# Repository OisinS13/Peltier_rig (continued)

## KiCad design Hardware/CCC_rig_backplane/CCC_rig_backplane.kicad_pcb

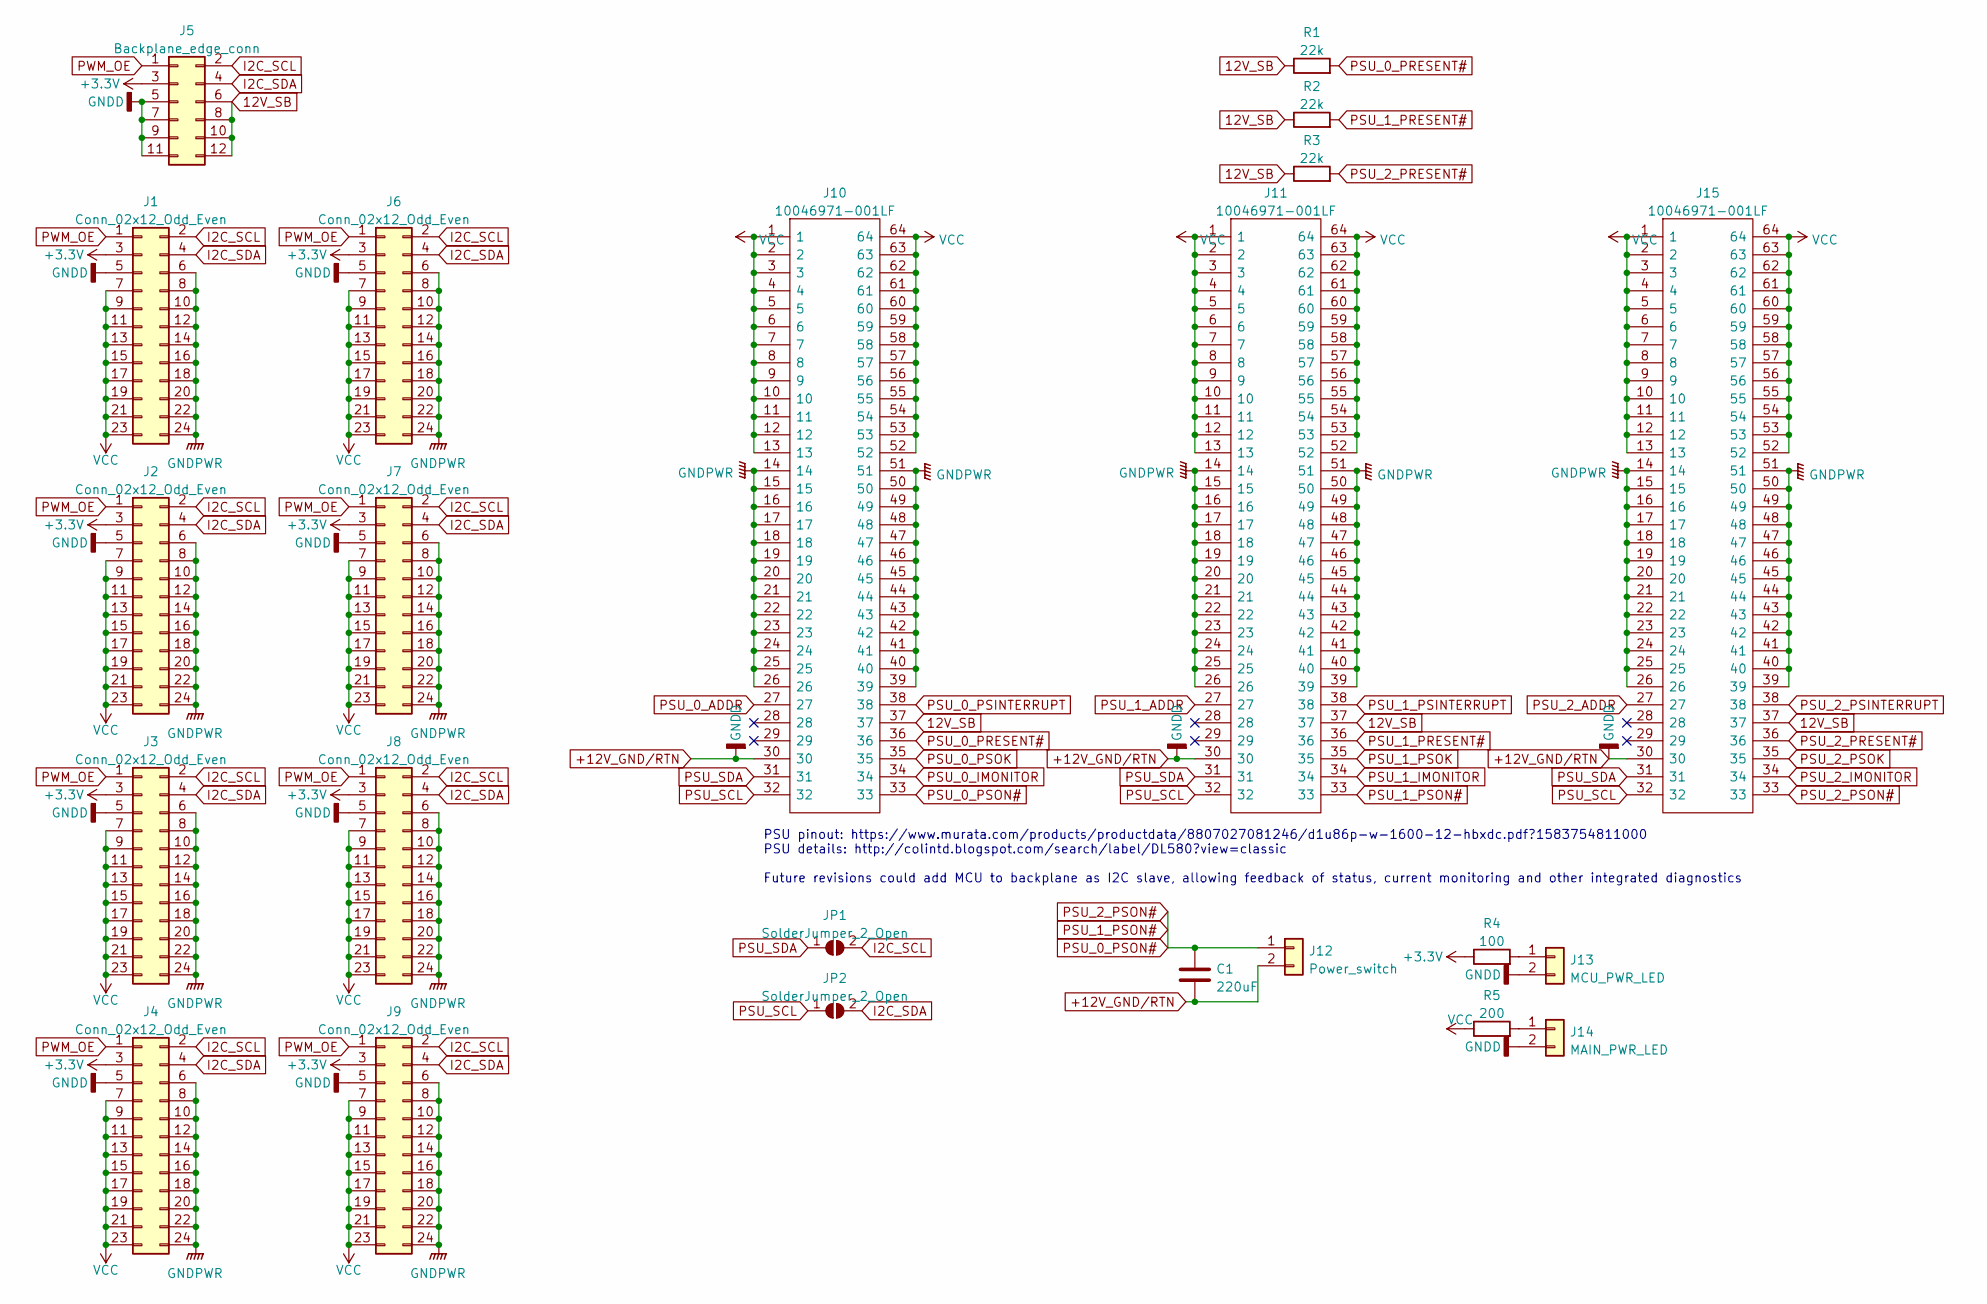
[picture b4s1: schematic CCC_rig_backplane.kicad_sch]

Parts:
C1: 220uF; CP_Radial_D8.0mm_P3.50mm
J1, J2, J3, J4, J6, J7, J8, J9: Conn_02x12_Odd_Even; 55308431
J5: Backplane_edge_conn; 755308435
J10, J11, J15: 10046971-001LF; RHDR64W90P508X254_2X32_8786X929X1549P; Mouser Part Number 649-10046971-001LF
J12: Power_switch; 1963531
J13: MCU_PWR_LED; 1963531
J14: MAIN_PWR_LED; 1963531
JP1, JP2: SolderJumper_2_Open; SolderJumper-2_P1.3mm_Open_RoundedPad1.0x1.5mm
R1, R2, R3: 22k; R_Axial_DIN0207_L6.3mm_D2.5mm_P7.62mm_Horizontal
R4: 100; R_Axial_DIN0207_L6.3mm_D2.5mm_P7.62mm_Horizontal
R5: 200; R_Axial_DIN0207_L6.3mm_D2.5mm_P7.62mm_Horizontal

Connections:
12V_SB: J5.6, J5.8, J5.10, J5.12, J10.37, J11.37, J15.37, R1.1, R2.1, R3.1
+3.3V: J1.3, J2.3, J3.3, J4.3, J5.3, J6.3, J7.3, J8.3, J9.3, R4.1
+12V_GND/RTN: C1.2, J1.5, J2.5, J3.5, J4.5, J5.5, J5.7, J5.9, J5.11, J6.5, J7.5, J8.5, J9.5, J10.30, J11.30, J12.2, J13.2, J14.2, J15.30
GNDPWR: J1.6, J1.8, J1.10, J1.12, J1.14, J1.16, J1.18, J1.20, J1.22, J1.24, J2.6, J2.8, J2.10, J2.12, J2.14, J2.16, J2.18, J2.20, J2.22, J2.24, J3.6, J3.8, J3.10, J3.12, J3.14, J3.16, J3.18, J3.20, J3.22, J3.24, J4.6, J4.8, J4.10, J4.12, J4.14, J4.16, J4.18, J4.20, J4.22, J4.24, J6.6, J6.8, J6.10, J6.12, J6.14, J6.16, J6.18, J6.20, J6.22, J6.24, J7.6, J7.8, J7.10, J7.12, J7.14, J7.16, J7.18, J7.20, J7.22, J7.24, J8.6, J8.8, J8.10, J8.12, J8.14, J8.16, J8.18, J8.20, J8.22, J8.24, J9.6, J9.8, J9.10, J9.12, J9.14, J9.16, J9.18, J9.20, J9.22, J9.24, J10.14, J10.15, J10.16, J10.17, J10.18, J10.19, J10.20, J10.21, J10.22, J10.23, J10.24, J10.25, J10.26, J10.39, J10.40, J10.41, J10.42, J10.43, J10.44, J10.45, J10.46, J10.47, J10.48, J10.49, J10.50, J10.51, J11.14, J11.15, J11.16, J11.17, J11.18, J11.19, J11.20, J11.21, J11.22, J11.23, J11.24, J11.25, J11.26, J11.39, J11.40, J11.41, J11.42, J11.43, J11.44, J11.45, J11.46, J11.47, J11.48, J11.49, J11.50, J11.51, J15.14, J15.15, J15.16, J15.17, J15.18, J15.19, J15.20, J15.21, J15.22, J15.23, J15.24, J15.25, J15.26, J15.39, J15.40, J15.41, J15.42, J15.43, J15.44, J15.45, J15.46, J15.47, J15.48, J15.49, J15.50, J15.51
I2C_SCL: J1.2, J2.2, J3.2, J4.2, J5.2, J6.2, J7.2, J8.2, J9.2, JP1.2 (B)
I2C_SDA: J1.4, J2.4, J3.4, J4.4, J5.4, J6.4, J7.4, J8.4, J9.4, JP2.2 (B)
unnamed: J13.1, R4.2
unnamed: J14.1, R5.2
PSU_0_ADDR: J10.27
PSU_0_IMONITOR: J10.34
PSU_0_PRESENT#: J10.36, R1.2
PSU_0_PSINTERRUPT: J10.38
PSU_0_PSOK: J10.35
PSU_0_PSON#: C1.1, J10.33, J11.33, J12.1, J15.33
PSU_1_ADDR: J11.27
PSU_1_IMONITOR: J11.34
PSU_1_PRESENT#: J11.36, R2.2
PSU_1_PSINTERRUPT: J11.38
PSU_1_PSOK: J11.35
PSU_2_ADDR: J15.27
PSU_2_IMONITOR: J15.34
PSU_2_PRESENT#: J15.36, R3.2
PSU_2_PSINTERRUPT: J15.38
PSU_2_PSOK: J15.35
PSU_SCL: J10.32, J11.32, J15.32, JP2.1 (A)
PSU_SDA: J10.31, J11.31, J15.31, JP1.1 (A)
PWM_OE: J1.1, J2.1, J3.1, J4.1, J5.1, J6.1, J7.1, J8.1, J9.1
VCC: J1.7, J1.9, J1.11, J1.13, J1.15, J1.17, J1.19, J1.21, J1.23, J2.7, J2.9, J2.11, J2.13, J2.15, J2.17, J2.19, J2.21, J2.23, J3.7, J3.9, J3.11, J3.13, J3.15, J3.17, J3.19, J3.21, J3.23, J4.7, J4.9, J4.11, J4.13, J4.15, J4.17, J4.19, J4.21, J4.23, J6.7, J6.9, J6.11, J6.13, J6.15, J6.17, J6.19, J6.21, J6.23, J7.7, J7.9, J7.11, J7.13, J7.15, J7.17, J7.19, J7.21, J7.23, J8.7, J8.9, J8.11, J8.13, J8.15, J8.17, J8.19, J8.21, J8.23, J9.7, J9.9, J9.11, J9.13, J9.15, J9.17, J9.19, J9.21, J9.23, J10.1, J10.2, J10.3, J10.4, J10.5, J10.6, J10.7, J10.8, J10.9, J10.10, J10.11, J10.12, J10.13, J10.52, J10.53, J10.54, J10.55, J10.56, J10.57, J10.58, J10.59, J10.60, J10.61, J10.62, J10.63, J10.64, J11.1, J11.2, J11.3, J11.4, J11.5, J11.6, J11.7, J11.8, J11.9, J11.10, J11.11, J11.12, J11.13, J11.52, J11.53, J11.54, J11.55, J11.56, J11.57, J11.58, J11.59, J11.60, J11.61, J11.62, J11.63, J11.64, J15.1, J15.2, J15.3, J15.4, J15.5, J15.6, J15.7, J15.8, J15.9, J15.10, J15.11, J15.12, J15.13, J15.52, J15.53, J15.54, J15.55, J15.56, J15.57, J15.58, J15.59, J15.60, J15.61, J15.62, J15.63, J15.64, R5.1

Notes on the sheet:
PSU pinout: https://www.murata.com/products/productdata/8807027081246/d1u86p-w-1600-12-hbxdc.pdf?1583754811000 PSU details: http://colintd.blogspot.com/search/label/DL580?view=classic Future revisions could add MCU to backplane as I2C slave, allowing feedback of status, current monitoring and other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

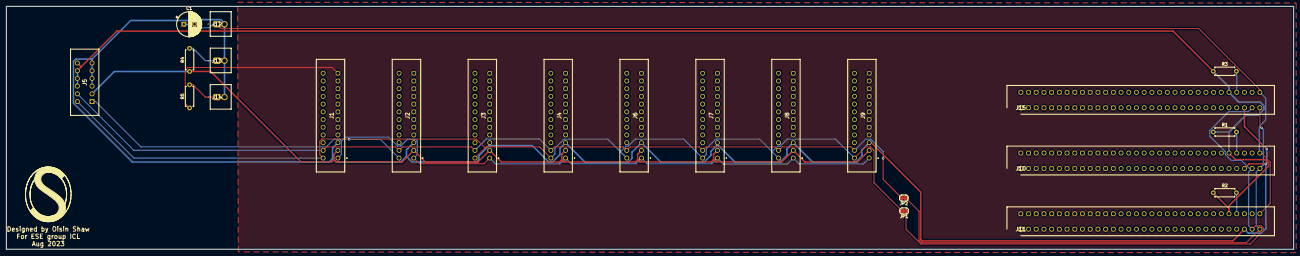
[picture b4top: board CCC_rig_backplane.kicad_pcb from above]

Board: 2 copper layers, 424.0 x 80.0 mm, 23 parts (0 on the bottom side), 16 nets.

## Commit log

2023-09-12 Add files via upload
    V.0.1 Initial pass at main functions
2023-09-13 Initial commit - WIP
2023-09-18 Add get, set, start, stop functions, WIP
2023-09-28 Can send and receive messages to specific channels
2023-09-28 Get function can retrieve and print variable
2023-09-28 Get and set functionality working for single variable
2023-09-28 Replaced separate get and set functions with single interface function
2023-09-29 Fully functional for all variables
2023-09-29 Start and stop commands added
2023-09-29 Added print of all running channels after start/stop command
2023-09-29 Reorganised and renamed functions
2023-09-29 Add serial commands functions to setup
2023-09-29 Uncomment save_settings
2023-11-01 Send absolute PID values to PWM drivers
2023-11-01 Command functions update existing values, implement PID settings directly
